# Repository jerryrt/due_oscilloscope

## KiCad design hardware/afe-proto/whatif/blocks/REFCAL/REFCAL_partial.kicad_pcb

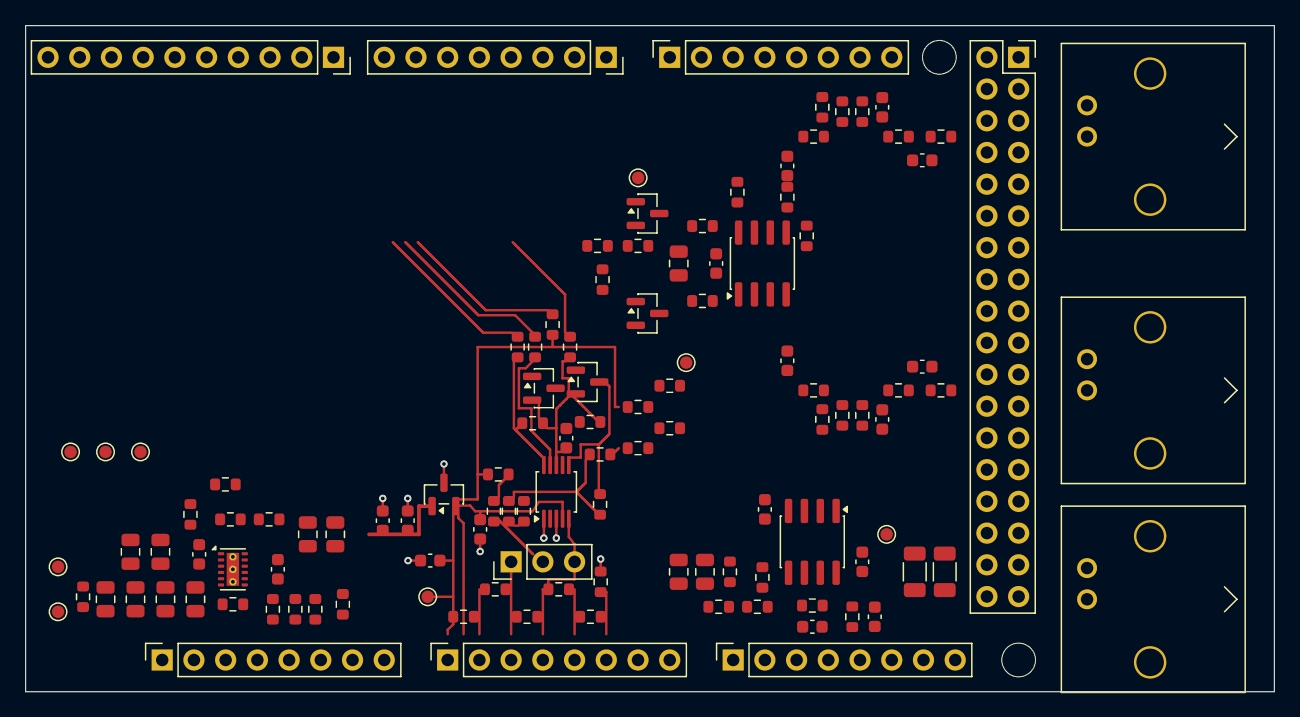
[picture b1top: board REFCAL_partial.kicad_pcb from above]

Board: 2 copper layers, 100.0 x 53.3 mm, 120 parts (0 on the bottom side), 60 nets.

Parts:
C101, C201: 12p C0G; C_0603_1608Metric
C102, C202: 30p C0G; C_0603_1608Metric
C103, C302, C303, C401, C501, C502, C503: 100n X7R; C_0603_1608Metric
C104, C305, C306, C403, C404, C405, C406, C407, C408, C409, C410: 10u X5R 25V; C_0805_2012Metric
C105, C203, C301, C304: 10p C0G; C_0603_1608Metric
C402, C504, C505: 1u X5R; C_0603_1608Metric
D101, D201, D501, D502: BAV99; SOT-23
J101, J201, J301: KH-BNC50-3511; BNC_Kinghelm_KH-BNC50-3511_Horizontal
J501: CAL; PinHeader_1x03_P2.54mm_Vertical
J601: POWER0; PinSocket_1x08_P2.54mm_Vertical
J602: ADCL0; PinSocket_1x08_P2.54mm_Vertical
J603: ADCH0; PinSocket_1x08_P2.54mm_Vertical
J604: PWML0; PinSocket_1x08_P2.54mm_Vertical
J605: COMMUNICATION0; PinSocket_1x08_P2.54mm_Vertical
J606: PWMH0; PinSocket_1x10_P2.54mm_Vertical
J607: XIO0; PinSocket_2x18_P2.54mm_Vertical_DueXIO
MH601, MH602: M2.5 standoff; MountingHole_2.7mm_M2.5
R101, R104, R201, R204, R403, R404, R405: 330k 1%; R_0603_1608Metric
R102, R105, R202, R205: 470k 1%; R_0603_1608Metric
R103, R203: 300k 1%; R_0603_1608Metric
R106, R206: 680 1%; R_0603_1608Metric
R107, R207: 22 1%; R_0603_1608Metric
R108, R408: 1 1%; R_0603_1608Metric
R109, R110, R111, R112, R113, R309, R310, R410, R515, R516, R517, R518, R519, R520: 0R 1%; R_0603_1608Metric
R301, R402, R406: 75k 1%; R_0603_1608Metric
R302: 4.99k 1%; R_0603_1608Metric
R303: 3.3k 1%; R_0603_1608Metric
R304, R306: 100 1% 1206; R_1206_3216Metric
R305, R308: 51k 1%; R_0603_1608Metric
R307, R503: 100 1%; R_0603_1608Metric
R401, R409: 100k 1%; R_0603_1608Metric
R407: 2.2k 1%; R_0603_1608Metric
R501: 22k 1%; R_0603_1608Metric
R502: 15k 1%; R_0603_1608Metric
R504, R505, R506, R507, R508: 270 1%; R_0603_1608Metric
R509, R511: 4.7k 1%; R_0603_1608Metric
R510: 0R; R_0603_1608Metric
R512: 1k 1%; R_0603_1608Metric
R513: 3.9k 1%; R_0603_1608Metric
R514: 13k 1%; R_0603_1608Metric
TP101: A1; TestPoint_Pad_D1.0mm
TP201: A0; TestPoint_Pad_D1.0mm
TP301: AWG_OUT; TestPoint_Pad_D1.0mm
TP401: +5V_DUE; TestPoint_Pad_D1.0mm
TP402: +5V_F; TestPoint_Pad_D1.0mm
TP403: GND; TestPoint_Pad_D1.0mm
TP404: +3V3A; TestPoint_Pad_D1.0mm
TP405: VNEG; TestPoint_Pad_D1.0mm
TP501: VREF; TestPoint_Pad_D1.0mm
U101, U301: TPH2502-SR; SOIC-8_3.9x4.9mm_P1.27mm
U401: LM27762DSSR; WSON-12-1EP_3x2mm_P0.5mm_EP1x2.65_ThermalVias
U501: REF3030EAIDBZR; SOT-23
U502: ADS1115IDGSR; TSSOP-10_3x3mm_P0.5mm

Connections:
/+3V3A: C302.1, C407.1, C408.1, C501.1, C505.1, R109.1, R406.1, R407.1, R517.1, TP404.1, U301.8, U401.11, U501.1
/+5V_DUE: J601.5, R408.1, TP401.1
/+5V_F: C401.1, C403.1, C404.1, R408.2, TP402.1, U401.3, U401.8, U401.12
/A0: D201.3, J602.8, R207.2, TP201.1
/A1: D101.3, J602.7, R107.2, TP101.1
/AREF: J606.8, R510.2
/AWG_BIN: C304.2, R305.2, R308.1, U301.5
/AWG_BNC: J301.1, R304.2, R306.2, R310.2
/AWG_BPL: R301.1, R308.2
/AWG_I: R309.2, R310.1
/AWG_INV: C301.2, R302.1, R303.2, U301.6
/AWG_OUT: C301.1, R303.1, R304.1, R306.1, TP301.1, U301.7
/AWG_S: R309.1, R501.1
/AWG_SP: U301.1, U301.2
/AWG_X: C305.1, C306.1, R302.2, R307.2
/CH1_IN: C101.1, J101.1, R102.1
/CH1_N: C101.2, C102.1, R103.2, R104.1, R105.1, R106.1
/CH1_NP: C105.1, R106.2, U101.5
/CH1_OUT: R107.1, U101.6, U101.7
/CH1_R1A: R102.2, R103.1
/CH1_R2A: R101.1, R105.2
/CH2_IN: C201.1, J201.1, R202.1
/CH2_N: C201.2, C202.1, R203.2, R204.1, R205.1, R206.1
/CH2_NP: C203.1, R206.2, U101.3
/CH2_OUT: R207.1, U101.1, U101.2
/CH2_R1A: R202.2, R203.1
/CH2_R2A: R201.1, R205.2
/DAC0: C304.1, J603.5, R305.1
/GND: C102.2, C103.2, C104.2, C105.2, C202.2, C203.2, C302.2, C303.2, C305.2, C306.2, C401.2, C403.2, C404.2, C405.2, C406.2, C407.2, C408.2, C409.2, C410.2, C501.2, C502.2, C503.2, C504.2, C505.2, D101.1, D201.1, D501.1, D502.1, J101.2, J201.2, J301.2, J601.6, J601.7, J606.7, J607.35, J607.36, R101.2, R201.2, R301.2, R401.2, R403.2, R404.2, R405.2, R407.2, R503.2, TP403.1, U101.4, U301.3, U401.1, U401.4, U401.13, U501.3, U502.1, U502.3
/LM_C1N: C402.2, U401.9
/LM_C1P: C402.1, U401.10
/LM_CP: C405.1, C406.1, U401.5
/LM_FBN: R402.2, R403.1, R404.1, R405.1, U401.7
/LM_FBP: R401.1, R409.2, U401.2
/LM_FBPX: R406.2, R409.1
/P33_R: C502.1, D501.2, D502.2, R509.2, R511.2, R517.2, U502.8
/P33_S: R109.2, R110.1
/P33_U: D101.2, D201.2, R108.1, R110.2
/SCL1: J606.10, R519.1
/SCL1_A: R511.1, R519.2, U502.10
/SC_VCC: C103.1, C104.1, R108.2, U101.8
/SDA1: J606.9, R518.1
/SDA1_A: R509.1, R518.2, U502.9
/SNS_B: J501.2, R502.2, R514.1, R520.1
/SNS_BI: D501.3, R514.2, U502.7
/SNS_B_N: R512.1, R520.2
/SNS_TAP: R501.2, R502.1, R513.1
/SNS_TI: D502.3, R513.2, U502.6
/TAP1: J602.6, R503.1, R504.1
/TAP2: J602.5, R504.2, R505.1
/TAP3: J501.3, J602.4, R505.2, R506.1, U502.5
/TAP4: J501.1, J602.3, R506.2, R507.1
/TAP5: J602.2, R507.2, R508.1
/VNEG: C303.1, C409.1, C410.1, R402.1, R410.1, R410.2, TP405.1, U301.4, U401.6
/VREF: C503.1, C504.1, J602.1, R307.1, R508.2, R510.1, R512.2, R515.1, TP501.1, U501.2, U502.4
/VREF_M: R515.2, R516.1
/VREF_P: R111.1, R204.2, R516.2
/VREF_Q: R111.2, R113.1
/VREF_R: R104.2, R112.2
/VREF_S: R112.1, R113.2

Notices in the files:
hardware/afe-proto/whatif/blocks/REFCAL/REFCAL_partial.kicad_pcb:
Own work, CC BY-SA 4.0
